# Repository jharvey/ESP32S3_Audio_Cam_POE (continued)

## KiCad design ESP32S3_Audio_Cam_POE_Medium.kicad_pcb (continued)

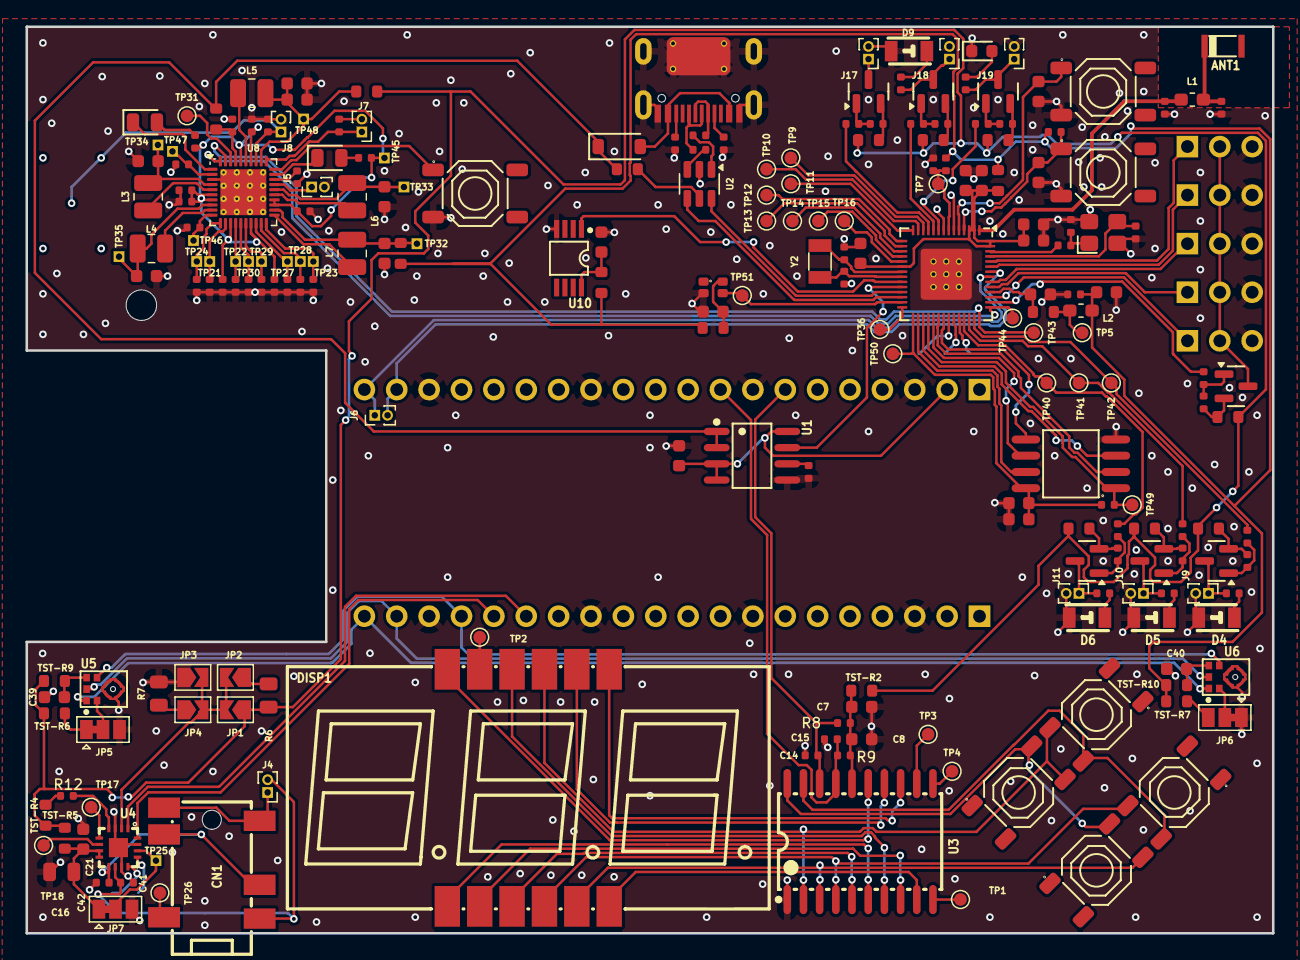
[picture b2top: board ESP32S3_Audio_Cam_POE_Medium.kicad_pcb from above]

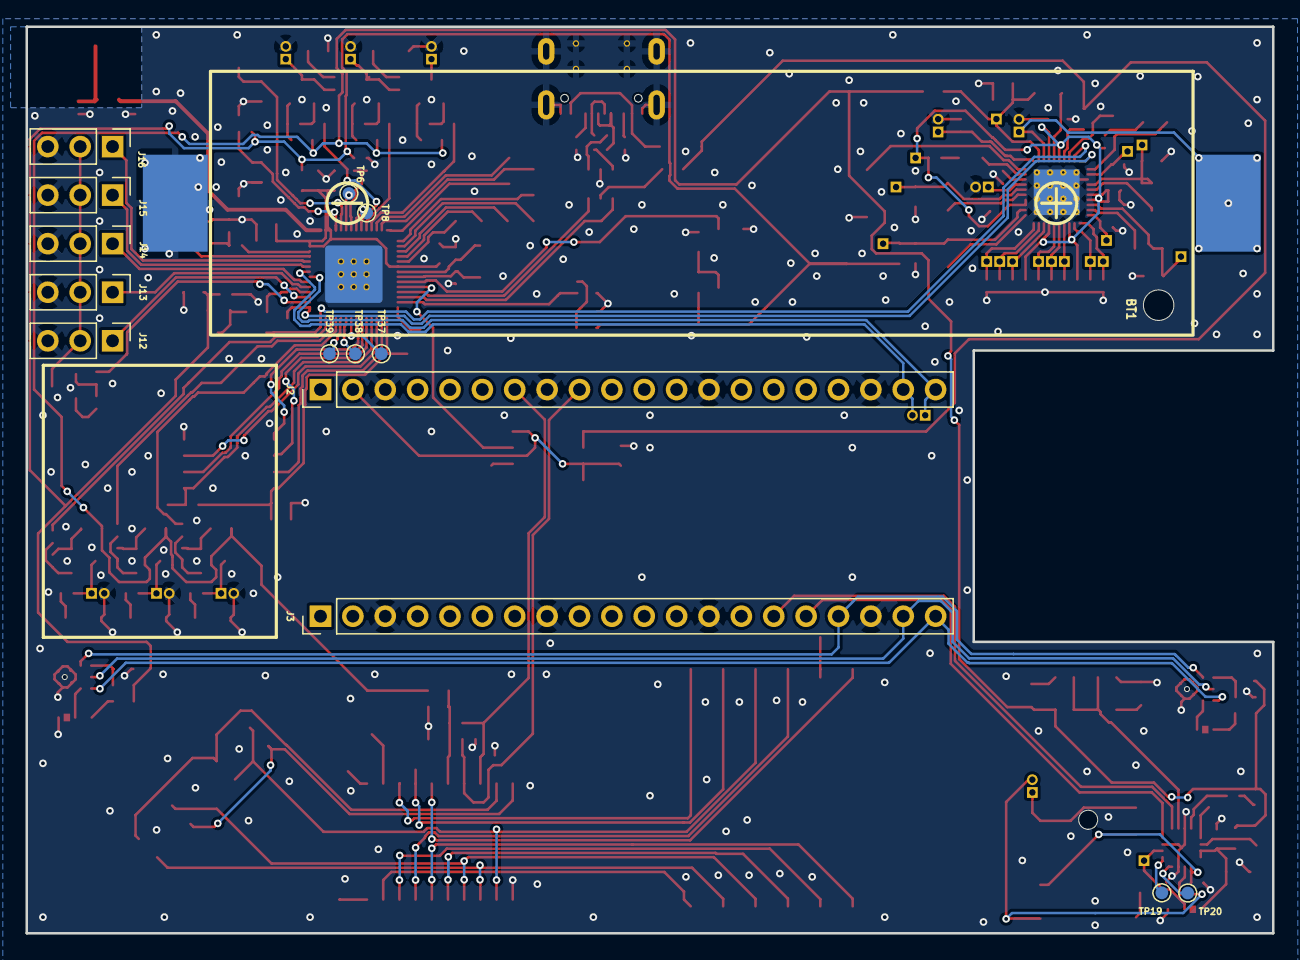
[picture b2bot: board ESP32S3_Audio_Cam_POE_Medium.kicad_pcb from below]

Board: 2 copper layers, 97.8 x 71.1 mm, 238 parts (15 on the bottom side), 175 nets.

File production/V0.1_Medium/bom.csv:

Designator,Footprint,Quantity,Value,LCSC Part #
ANT1,ANT-SMD_L3.2-W1.6-KH-3216F245C04,1,KH-3216-H0209,
"BOOT1, PB1, PB2, PB3, PB4, PB5, RST1",SW-SMD_4P-L5.1-W5.1-P3.70-LS6.5-TL-2,7,"Tactile Button, 160gf",C318884
BT1,BATTERY-SMD_18650-1S-L77.1-W20.7-1,1,BH-18650-B1BA002,C2988620
C1,C_0402,1,1nF,C1523
"C10, C11",C_0402,2,3.3pF,C1565
"C12, C21, C3, C35, C36, C37, C38, C39, C40, C52, C54, C55, C56, C57, C8, C9",C_0603,16,100nF,C14663
"C13, C44",C_0402,2,10uF,C15525
"C14, C15",C_0402,2,100pF,C1546
C16,C_0805,1,10uF,C440198
"C17, C18, C20, C22, C43, C50, C51",C_0402,7,1uF,C52923
C19,C_0402,1,4.7uF,C23733
"C2, C4",C_0402,2,10pF,C32949
"C23, C24, C45, C46, C47, C48",C_0603,6,22uF,C59461
"C25, C26, C27, C28, C29, C30, C31, C32, C33, C49",C_0402,10,2.2uF,C12530
"C34, C53, C7",C_0603,3,1uF,C15849
"C41, C42",C_0402,2,220pF,C1530
"C5, C6",C_0402,2,20pF,C1554
CN1,SMD_3.5mm_Audio_Connectors_(Headphones)_C707223,1,PJ-316C-6A,C707223
D1,D_SOD-123,1,1N4148W,C81598
D2,D_0805,1,Yellow,C2296
D3,D_0805,1,Green,C2297
"D4, D5, D6, D9",IR-LED_C131280,4,IR,C131280
D7,LED-SMD_4P-L1.6-W1.5_XL-1615RGBC-WS2812B,1,WS2812B,C5349954
D8,D_0603,1,White,C2290
DISP1,3x7-seg_LED-RED_C2913084,1,SLS0563DRA1GD,C2913084
J1,TYPE-C-SMD_HX-TYPE-C-16PIN,1,"Connector, USB-TYPE-C-16P",C2927039
"J10, J11, J17, J18, J19, J4, J5, J6, J7, J8, J9",PinHeader_1x02_P1.00mm_Vertical,11,Conn_01x02,
"J12, J13, J14, J15, J16",PinHeader_1x03_P2.54mm_Vertical,5,Conn_01x03,
"J2, J3",PinHeader_1x20_P2.54mm_Vertical,2,Conn_01x20_Pin,
"L1, L2",0603,2,2nH,
"L3, L4, L5, L6, L7",1008,5,"1uH,3.3A",C435392
NTC1,R_0402,1,NTC,C3018545 
"Q1, Q2, Q3, Q4, Q5, Q6, Q7",Q_SOT-23,7,AO3401A,C15127
R1,R_0402,1,22Ω,C25092
"R10, R15",R_0402,2,100kΩ,C25741
"R11, R13, R14, R22, R23, R24, R27, R34, R35, R8, R9",R_0402,11,10kΩ,C25744
"R12, R19, R20, R21, R26, R31, R32, R33",R_0402,8,1MΩ,C26083
"R16, R17, R18, R25, R28, R29, R30",R_0402,7,10MΩ,C26082
"R2, R3",R_0402,2,5.1kΩ,C25905
"R4, R5",R_0402,2,33Ω,C25105
"R6, R7",R_0805,2,100kΩ,C149504
"TP1, TP10, TP11, TP12, TP13, TP14, TP15, TP16, TP17, TP18, TP19, TP2, TP20, TP26, TP3, TP31, TP36, TP37, TP38, TP39, TP4, TP40, TP41, TP42, TP43, TP44, TP49, TP5, TP50, TP51, TP6, TP7, TP8, TP9",TestPoint_Pad_D1.0mm,34,TestPoint,
"TP21, TP22, TP23, TP24, TP25, TP27, TP28, TP29, TP30, TP32, TP33, TP34, TP35, TP45, TP46, TP47, TP48",PinHeader_1x01_P1.00mm_Vertical,17,TestPoint,
"TST-R1, TST-R10, TST-R11, TST-R12, TST-R13, TST-R14, TST-R15, TST-R16, TST-R17, TST-R18, TST-R19, TST-R2, TST-R20, TST-R21, TST-R22, TST-R3, TST-R4, TST-R5, TST-R6, TST-R7, TST-R8, TST-R9",R_0603,22,0Ω,C21189
U1,Current-sensor_MT9221CT-06BR5_C879632,1,MT9221CT-06BR5,C879632
U10,DS18B20_C695836,1,DS18B20U(UMW),C695836
U2,SOT-23-6,1,USBLC6-2SC6,
U3,digital tube drivers_c2962580,1,TM1637,C2962580
U4,MAX98357AETE+T_C910544,1,MAX98357AETE+T,
"U5, U6",ICS-43434_C5656610,2,ICS-43434,C5656610
U7,QFN-56-1EP_7x7mm_P0.4mm_EP4x4mm_ThermalVias,1,ESP32-S3,C2913194 
U8,QFN-40-1EP_5x5mm_P0.4mm_EP3.6x3.6mm_ThermalVias,1,AXP2101,C3036461
U9,SOIC-8_L5.3-W5.3-P1.27-LS8.0-BL,1,W25Q128JVSIQ,
Y1,OSC-SMD_4P-L3.2-W2.5-BL_SIT8008BI,1,"40MHz, 15pF",C9010
Y2,Crystal_SMD_3215-2Pin_3.2x1.5mm,1,32.768KHz,

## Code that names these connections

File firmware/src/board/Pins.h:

// ESP32-S3 (U7) pin map, taken from the v0.1b schematic netlist (2026-11-12).
// Regenerate this if the schematic changes.
#pragma once

namespace pins {

// I2C bus: PCA9685 0x40 (U20), TCA9555 0x20 (U21), AXP2101 0x34 (U18)
constexpr int I2C_SCL = 43;
constexpr int I2C_SDA = 44;

// Shared SPI: W5500 Ethernet (U9) and RFM95 LoRa (U19)
constexpr int SPI_MOSI = 11;
constexpr int SPI_MISO = 12;
constexpr int SPI_SCLK = 13;
constexpr int ETH_CS = 14;
constexpr int LORA_CS = 9;
constexpr int LORA_DIO0 = 15;  // LORA_IRQ

// PDM microphones U16/U17 (L/R by JP7/JP8) on I2S0
constexpr int MIC_CLK = 10;
constexpr int MIC_DATA = 7;

// Speaker amp MAX98357A (U15) on I2S1
constexpr int SPK_BCLK = 16;  // net /ESP.MIC.SCK
constexpr int SPK_WS = 8;     // net /ESP.I2S.WS
constexpr int SPK_DOUT = 21;  // net /SPK.DIN

// SD card, SDMMC 1-bit (DAT3 pulled up by R29, not on a GPIO)
constexpr int SD_CLK = 5;
constexpr int SD_CMD = 6;
constexpr int SD_D0 = 4;

// Camera (OV2640 / OV5640). No PWDN/RESET GPIOs; power via TCA9555 P03.
constexpr int CAM_XCLK = 3;
constexpr int CAM_SIOD = 47;  // CAM.SDA
constexpr int CAM_SIOC = 48;  // CAM.SCL
constexpr int CAM_VSYNC = 1;
constexpr int CAM_HREF = 2;
constexpr int CAM_PCLK = 39;
constexpr int CAM_D0 = 41, CAM_D1 = 45, CAM_D2 = 46, CAM_D3 = 42;
constexpr int CAM_D4 = 40, CAM_D5 = 38, CAM_D6 = 17, CAM_D7 = 18;
// NOTE: GPIO45 and GPIO46 are strapping pins. GPIO45 selects the VDD_SPI voltage at reset;
// if the camera (now always powered) drives D1 high during a reset, the chip picks 1.8 V
// flash and fails to boot. Burn the VDD_SPI_FORCE / VDD_SPI_TIEH eFuses at provisioning,
// or move those camera data lines in the next board spin.

// TCA9555 (U21) port bits
namespace exp {
constexpr int TM_CLK = 0;      // P00  TM1637 CLK (display + key scan)
constexpr int TM_DIO = 1;      // P01  TM1637 DIO
constexpr int ETH_RST = 2;     // P02  W5500 reset (via R27)
constexpr int CAM_PWR = 3;     // P03  camera power (Q1 via R15)
constexpr int LORA_RST = 4;    // P04
constexpr int PMU_IRQ = 5;     // P05  AXP2101 IRQ, input
constexpr int PWM_OE = 6;      // P06  PCA9685 /OE, high = outputs off
constexpr int ETH_INT = 7;     // P07  W5500 INT, input (W5500 runs polled)
}  // namespace exp

// PCA9685 (U20) channels, open-drain (MODE2.OUTDRV = 0)
namespace pwm {
constexpr int RC_PAN = 0, RC_TILT = 1, RC_ROT = 2, RC_OTHER = 3;  // servo signals, 4.7k pull-ups
constexpr int RC_PWR = 4;                                          // servo 5 V switch (Q2), low = on
constexpr int LED_WHITE = 5, LED_IR = 6, LED_OTHER = 7;            // lamp P-FETs, low = on
constexpr int MISC1 = 8, MISC2 = 9, MISC3 = 10;                    // MISC.OUT P-FETs (laser on one of these)
}  // namespace pwm

}  // namespace pins

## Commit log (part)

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2025-05-09 Initial draft commit. Non Functional.
2025-05-09 draft commit
2025-05-09 draft check in
2025-05-10 Draft commit, needs routing, schematic is probably mostly OK. Footprints are roughly located.
2025-05-22 draft commit, mostly added notes
2025-05-27 DRAFT added AXP2101 battery circuit
2025-05-28 DRAFT added misc outputs, PMU and resolved some TODO notes.
2025-05-30 DRAFT added mic jack.
2025-08-12 Draft Updated ESP32-S3 now includes 8MB internal PSRAM
2025-08-14 Draft Misc changes, layout still needs a lot of work.
2025-08-15 Draft misc layout, layout still needs a lot of work
2025-08-16 DRAFT commit, still needs lots of layout work.
2025-08-17 DRAFT commit, still needs lots of layout work. Everything connected, 70+ errors to resolve or ignore.
2025-08-18 Draft Commit, probably OK-ish. Lots of errors and warnings, but probably not important.
2025-08-24 DRAFT fixed many things with ANT1, added ANT2, moved MicJack to edge of PCB
2025-08-25 Added 1st spin files
2025-08-25 Added README.md
2025-08-26 DRAFT added smaller PCB design
2025-08-26 Draft smaller board.
2025-08-27 Draft
2025-08-27 Reverted Smaller
2025-08-27 Draft Medium
2025-08-28 Draft Medium re-annotated.
2025-08-29 Medium R0.1 production files created
2025-08-29 Updated name
2025-08-29 Added smaller production files.
2025-08-29 Changed Vdrive2 net from PMU.Vo1 to VDCDC5
2025-08-29 Changed input power from 3.3V to 5V.
2025-08-29 flipped RC servo headers to back side.
2025-09-02 Moved PCB edge to make easier to get SD card out.
2025-09-04 V0.1 updates added pictures and exported 3D file
2025-09-04 Updated PCB edge to allow easier access to SD card.
2025-09-04 updated smaller board layout
2025-12-02 Fix image paths in README for 3D pictures
2025-12-23 Added LORA module rough draft
2025-12-27 Draft commit added LORA
2026-01-19 Minor updates, looks like it's ready for 1st spin.
2026-01-19 added C107 to help with surge suppression
2026-01-20 Draft commit, added 33 ohms to camera lines to prevent cross talk
2026-06-14 updated to lower cost mic
2026-06-14 added mic.sck, mic.sd, and mic.ws term resistors
2026-06-14 moved nets off of conflicting psram IO.
2026-06-14 combined speaker and mic I2S signals making progress on IO count.
2026-06-14 re-connected digital signals now without conflict on PSRAM IO. Layout needs updating.
2026-06-14 updated pin out layout is now off of PSRAM IO.
2026-06-14 flipped D6 and D7 back to original pins, needed for internal connects.
